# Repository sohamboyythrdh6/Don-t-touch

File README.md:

# Don-t-touch
i made a little project which can prevent thief from broke into your house . it's really basic project i didn't use any microcontroler ir ic in this project

it can really useful for those people who's doors are really silent . in my project i use a TTP223 touch sensore . when someone touch the door metal part it instantly Triger the buzzer it even have reset button to stop the alarm.
to build this project you need all the components and pcb given in my BOM and pcb after getting all those parts you simpely need to solder everything on place and then scratch a little part on touch sensor and solder a wire wich connect to a metal part of your door metal part and turn on the switch that's all.

you might wondered how to connect the sensor with the door . its very simple at first place the TTP223 touch module at it's place then scratch a lil part of that sensor     

then connect a wire on it

at last connect the other end of the wire with any metal conductive part of your door

| Component | Purpose | Qty | Cost (USD) | Distributor |
|-----------|---------|-----|------------|-------------|
| Small Active Electromagnetic Buzzer | Audible warning indicator | 1 | $0.13 | Maker Bazar |
| 18650 SMD/SMT Battery Holder | Holds and connects the battery | 1 | $0.41 | Maker Bazar |
| 18650 Li-Ion Rechargeable Cell | Powers the circuit | 1 | $0.62 | Maker Bazar |
| 12×12mm Tactile Push Button | Reset button | 1 | $0.07 | Maker Bazar |
| 3-Pin DIP Mini Slide Switch | Power ON/OFF switch | 1 | $0.47 | Maker Bazar |
| BC547 Transistor | Electrically controls the switching circuit | 1 | $0.20 | Maker Bazar |
| Female Berg Strip 2.54mm Header | Connects the touch sensor | 3 | $0.09 | Maker Bazar |
| Capacitive Touch Sensor Module | Main touch sensor | 1 | $0.10 | Maker Bazar |
| 10kΩ Carbon Film Resistor | Current limiting and voltage biasing | 1 | $0.16 | Maker Bazar |
| 1kΩ Carbon Film Resistor | Current limiting and voltage biasing | 1 | $0.16 | Maker Bazar |
| Custom PCB | Mounts and connects all components | 1 | $4.00 | JLCPCB |
| Battery Charger | Charges the 18650 battery | 1 | $1.56 | Maker Bazar |
| Delivery Charges | Shipping costs | 1 | $10.00 | Various |

**Total Estimated Cost:** **$18.00 USD**

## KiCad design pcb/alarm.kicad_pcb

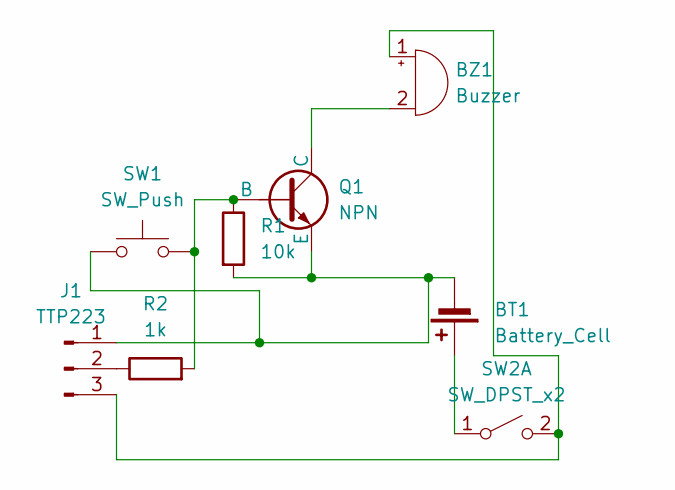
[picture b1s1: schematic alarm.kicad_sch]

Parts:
BT1: Battery_Cell; BatteryHolder_Keystone_1042_1x18650
BZ1: Buzzer; Buzzer_12x9.5RM7.6
J1: TTP223; PinSocket_1x03_P2.54mm_Vertical
Q1: NPN; TO-92_Inline
R1: 10k; R_Axial_DIN0204_L3.6mm_D1.6mm_P5.08mm_Horizontal
R2: 1k; R_Axial_DIN0204_L3.6mm_D1.6mm_P5.08mm_Horizontal
SW1: SW_Push; SW_PUSH-12mm
SW2: SW_DPST_x2; SW_Slide_SPDT_Straight_CK_OS102011MS2Q

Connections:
unnamed: BT1.1 (+), SW2.1 (A)
unnamed: BT1.2 (-), J1.1, Q1.3 (E), R1.2, SW1.1
unnamed: BZ1.1 (+), J1.3, SW2.2 (B)
unnamed: BZ1.2 (-), Q1.1 (C)
unnamed: J1.2, R2.1
unnamed: Q1.2 (B), R1.1, R2.2, SW1.2

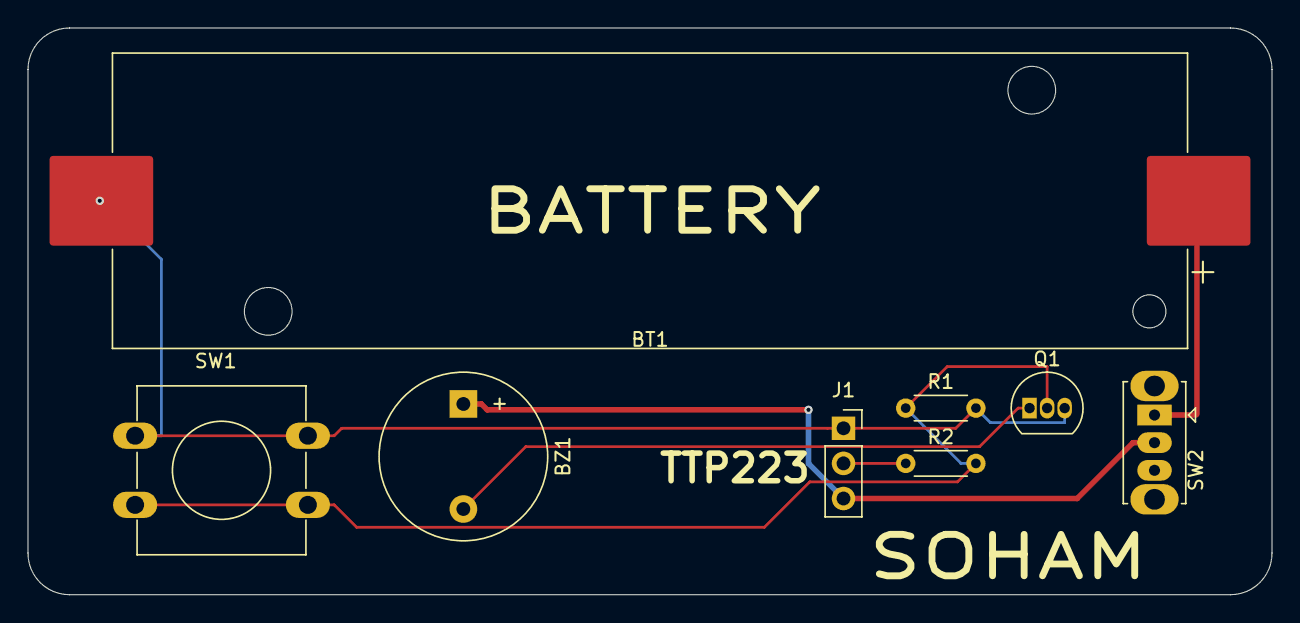
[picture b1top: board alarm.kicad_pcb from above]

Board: 2 copper layers, 90.0 x 41.0 mm, 8 parts (0 on the bottom side), 6 nets.

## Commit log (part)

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2026-05-03 Create s
2026-05-03 Create a
2026-05-04 Modify bom.csv to add usage and price dollar columns
    Updated bom.csv to include additional columns for price in dollars and usage descriptions for each component.
2026-05-13 Create 7
2026-05-13 Rename dont touch zine.png to Zine.png
